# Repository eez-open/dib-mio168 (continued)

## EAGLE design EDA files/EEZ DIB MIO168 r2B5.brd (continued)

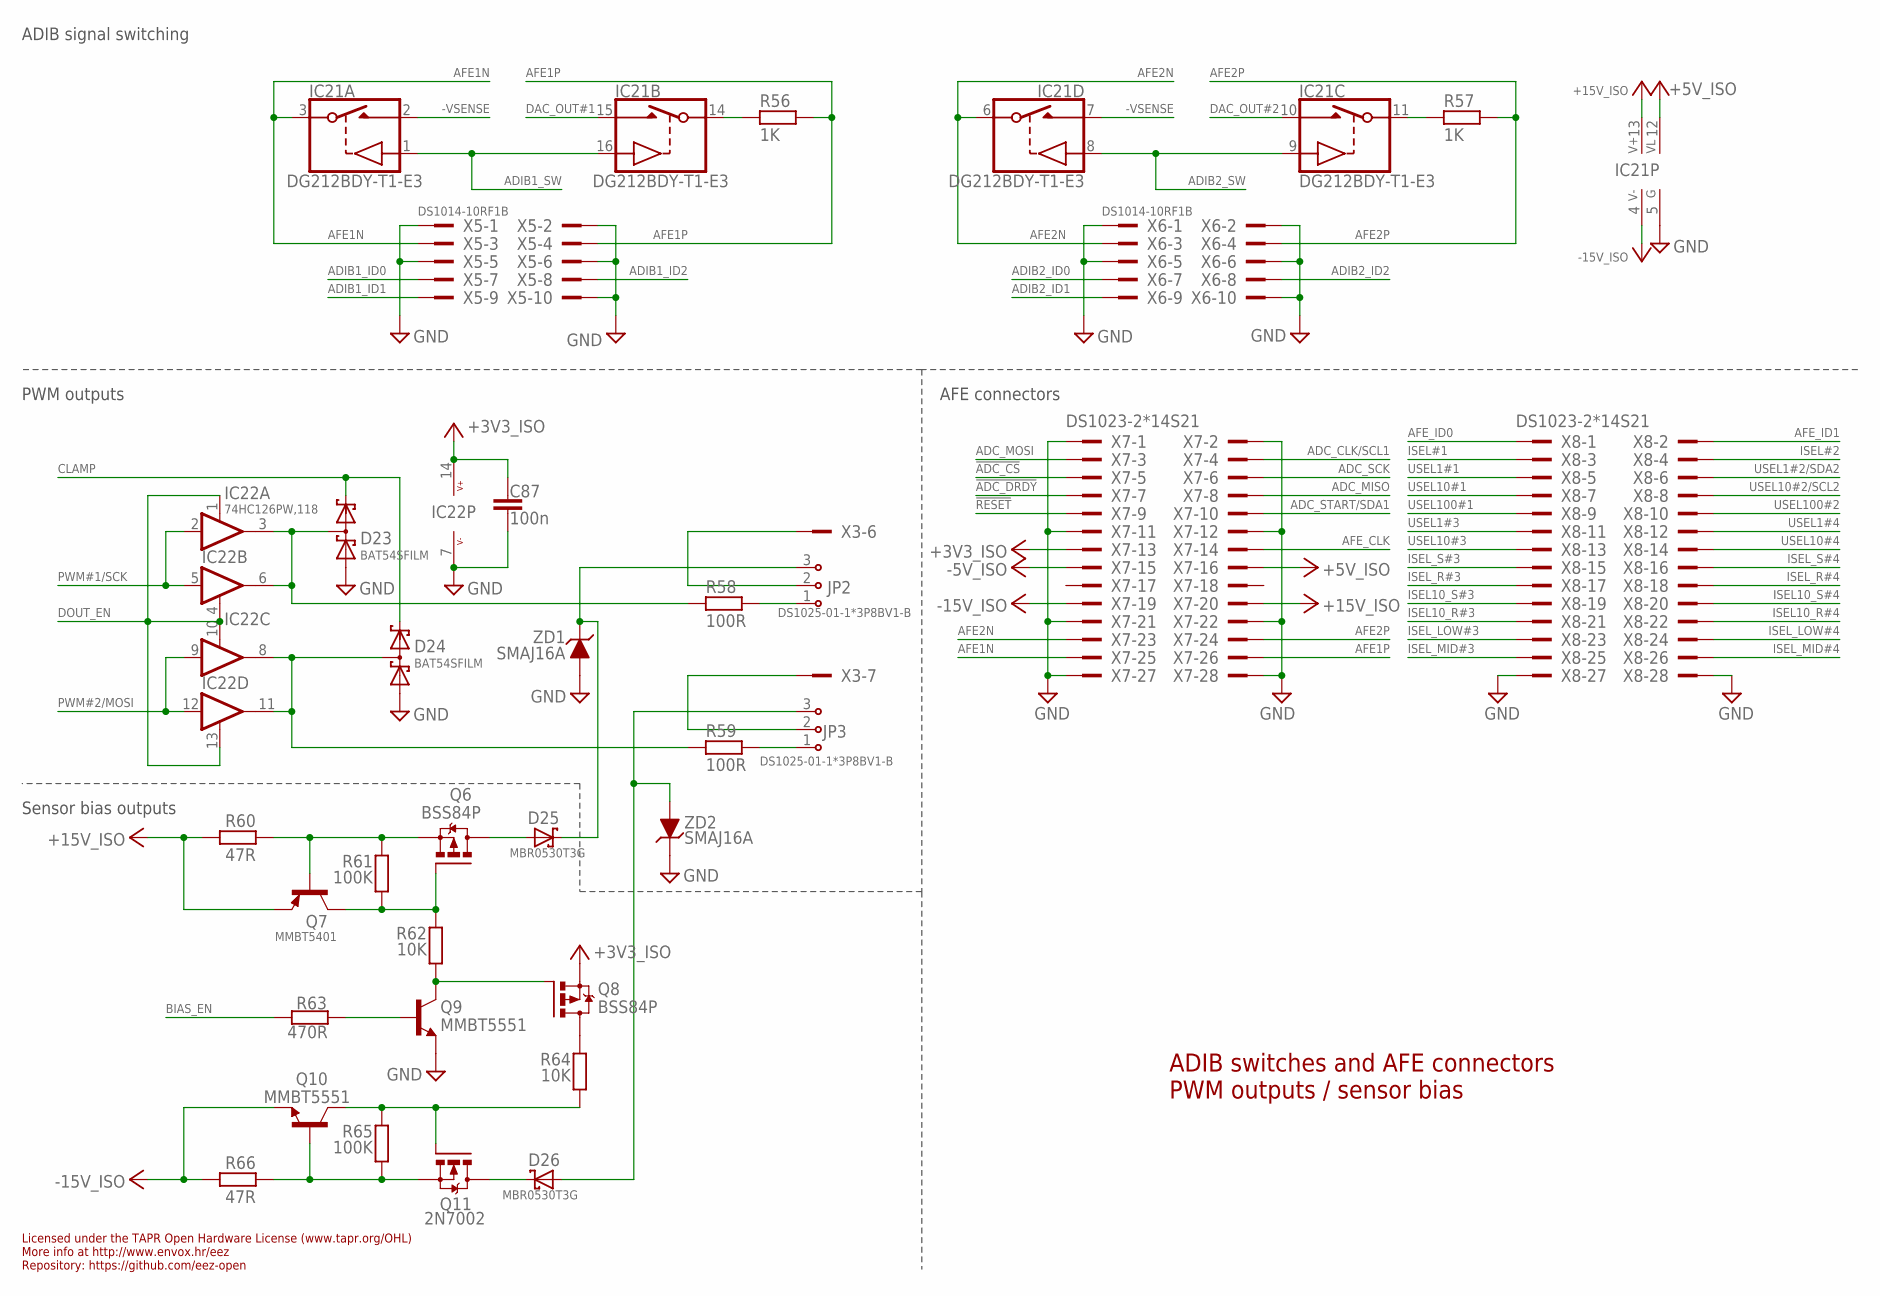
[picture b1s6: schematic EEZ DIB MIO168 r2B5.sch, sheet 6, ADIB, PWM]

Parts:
C87: 100n; C0603
D23, D24: BAT54SFILM; SOT23
D25, D26: MBR0530T3G; SOD123
IC21: DG212BDY-T1-E3; SO16
IC22: 74HC126PW,118; PW14
JP2, JP3: DS1025-01-1*3P8BV1-B; ZL303-03P
Q6, Q8: BSS84P; SOT95P237X112-3N
Q7: MMBT5401; SOT23-BEC
Q9, Q10: MMBT5551; SOT23-BEC
Q11: 2N7002; SOT103P240X110-3N
R56, R57: 1K; R0805
R58, R59: 100R; R0805
R60, R66: 47R; R0805
R61, R65: 100K; R0805
R62, R64: 10K; R0805
R63: 470R; R0805
X3: 691327310016
X5, X6: DS1014-10RF1B
X7, X8: DS1023-2*14S21; TSW-114-07-F-D
ZD1, ZD2: SMAJ16A; DO214AC

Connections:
!ADC_CS: X7.5; also elsewhere on the board
!ADC_DRDY: X7.7; also elsewhere on the board
!RESET: X7.9; also elsewhere on the board
+3V3_ISO: C87.2, IC22.14 (V+), Q8.2 (S), X7.13; also elsewhere on the board
+5V_ISO: IC21.12 (VL), X7.16; also elsewhere on the board
+15V_ISO: IC21.13 (V+), Q7.E, R60.1, X7.20; also elsewhere on the board
-5V_ISO: X7.15; also elsewhere on the board
-15V_ISO: IC21.4 (V-), Q10.E, R66.1, X7.19; also elsewhere on the board
-VSENSE: IC21.2 (D), IC21.7 (D); also elsewhere on the board
ADC_CLK/SCL1: X7.4; also elsewhere on the board
ADC_MISO: X7.8; also elsewhere on the board
ADC_MOSI: X7.3; also elsewhere on the board
ADC_SCK: X7.6; also elsewhere on the board
ADC_START/SDA1: X7.10; also elsewhere on the board
ADIB1_ID0: X5.7; also elsewhere on the board
ADIB1_ID1: X5.9; also elsewhere on the board
ADIB1_ID2: X5.8; also elsewhere on the board
ADIB1_SW: IC21.1 (IN), IC21.16 (IN); also elsewhere on the board
ADIB2_ID0: X6.7; also elsewhere on the board
ADIB2_ID1: X6.9; also elsewhere on the board
ADIB2_ID2: X6.8; also elsewhere on the board
ADIB2_SW: IC21.8 (IN), IC21.9 (IN); also elsewhere on the board
AFE1N: IC21.3 (S), X5.3, X7.25
AFE1P: R56.1, X5.4, X7.26
AFE2N: IC21.6 (S), X6.3, X7.23
AFE2P: R57.1, X6.4, X7.24
AFE_CLK: X7.14; also elsewhere on the board
AFE_ID0: X8.1; also elsewhere on the board
AFE_ID1: X8.2; also elsewhere on the board
BIAS_EN: R63.1; also elsewhere on the board
CLAMP: D23.2 (C2), D24.2 (C2); also elsewhere on the board
DAC_OUT#1: IC21.15 (D); also elsewhere on the board
DAC_OUT#2: IC21.10 (D); also elsewhere on the board
DOUT_EN: IC22.1 (EN), IC22.4 (EN), IC22.10 (EN), IC22.13 (EN); also elsewhere on the board
GND: C87.1, D23.1 (A1), D24.1 (A1), IC21.5 (GND), IC22.7 (V-), Q9.E, X5.1, X5.2, X5.5, X5.6, X5.10, X6.1, X6.2, X6.5, X6.6, X6.10, X7.1, X7.2, X7.11, X7.12, X7.21, X7.22, X7.27, X7.28, X8.27, X8.28, ZD1.A, ZD2.C; also elsewhere on the board
ISEL10_R#3: X8.21; also elsewhere on the board
ISEL10_R#4: X8.22; also elsewhere on the board
ISEL10_S#3: X8.19; also elsewhere on the board
ISEL10_S#4: X8.20; also elsewhere on the board
ISEL#1: X8.3; also elsewhere on the board
ISEL#2: X8.4; also elsewhere on the board
ISEL_LOW#3: X8.23; also elsewhere on the board
ISEL_LOW#4: X8.24; also elsewhere on the board
ISEL_MID#3: X8.25; also elsewhere on the board
ISEL_MID#4: X8.26; also elsewhere on the board
ISEL_R#3: X8.17; also elsewhere on the board
ISEL_R#4: X8.18; also elsewhere on the board
ISEL_S#3: X8.15; also elsewhere on the board
ISEL_S#4: X8.16; also elsewhere on the board
unnamed: Q9.B, R63.2
unnamed: JP2.1, R58.1
unnamed: JP3.1, R59.1
unnamed: IC21.14 (S), R56.2
unnamed: IC21.11 (S), R57.2
unnamed: JP2.2, X3.6
unnamed: JP3.2, X3.7
unnamed: D23.3 (C1A2), IC22.3 (O), IC22.6 (O), R58.2
unnamed: D24.3 (C1A2), IC22.8 (O), IC22.11 (O), R59.2
unnamed: Q8.1 (G), Q9.C, R62.2
unnamed: Q6.1 (G), Q7.C, R61.2, R62.1
unnamed: D25.A, Q6.3 (D)
unnamed: D25.C, JP2.3, ZD1.C
unnamed: Q6.2 (S), Q7.B, R60.2, R61.1
unnamed: Q10.C, Q11.1 (G), R64.2, R65.1
unnamed: Q10.B, Q11.2 (S), R65.2, R66.2
unnamed: Q8.3 (D), R64.1
unnamed: D26.C, Q11.3 (D)
unnamed: D26.A, JP3.3, ZD2.A
PWM#1/SCK: IC22.2 (I), IC22.5 (I); also elsewhere on the board
PWM#2/MOSI: IC22.9 (I), IC22.12 (I); also elsewhere on the board
USEL1#1: X8.5; also elsewhere on the board
USEL1#2/SDA2: X8.6; also elsewhere on the board
USEL1#3: X8.11; also elsewhere on the board
USEL1#4: X8.12; also elsewhere on the board
USEL10#1: X8.7; also elsewhere on the board
USEL10#2/SCL2: X8.8; also elsewhere on the board
USEL10#3: X8.13; also elsewhere on the board
USEL10#4: X8.14; also elsewhere on the board
USEL100#1: X8.9; also elsewhere on the board
USEL100#2: X8.10; also elsewhere on the board

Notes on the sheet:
Licensed under the TAPR Open Hardware License (www.tapr.org/OHL)
Repository: https://github.com/eez-open
More info at http://www.envox.hr/eez
ADIB switches and AFE connectors PWM outputs / sensor bias
ADIB signal switching
AFE connectors
PWM outputs
Sensor bias outputs

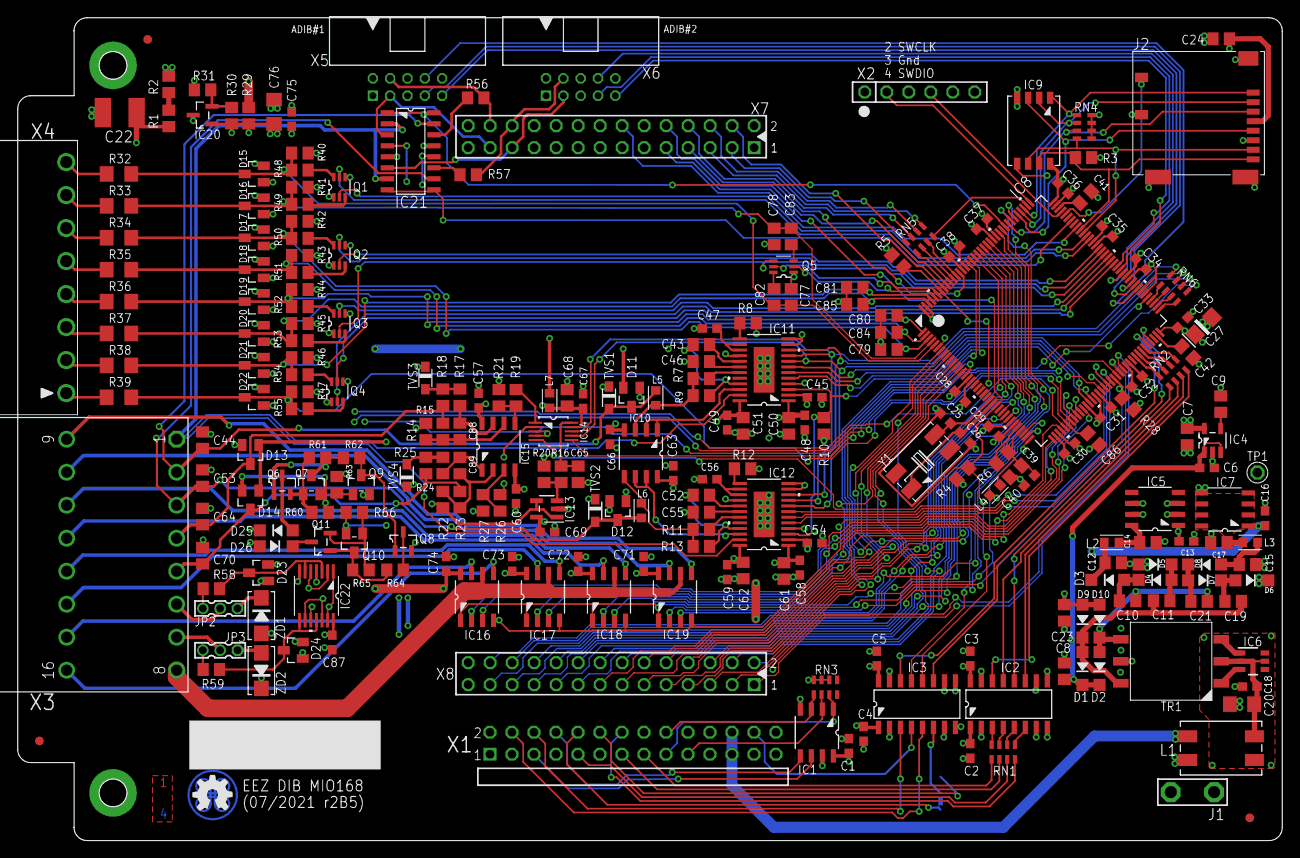
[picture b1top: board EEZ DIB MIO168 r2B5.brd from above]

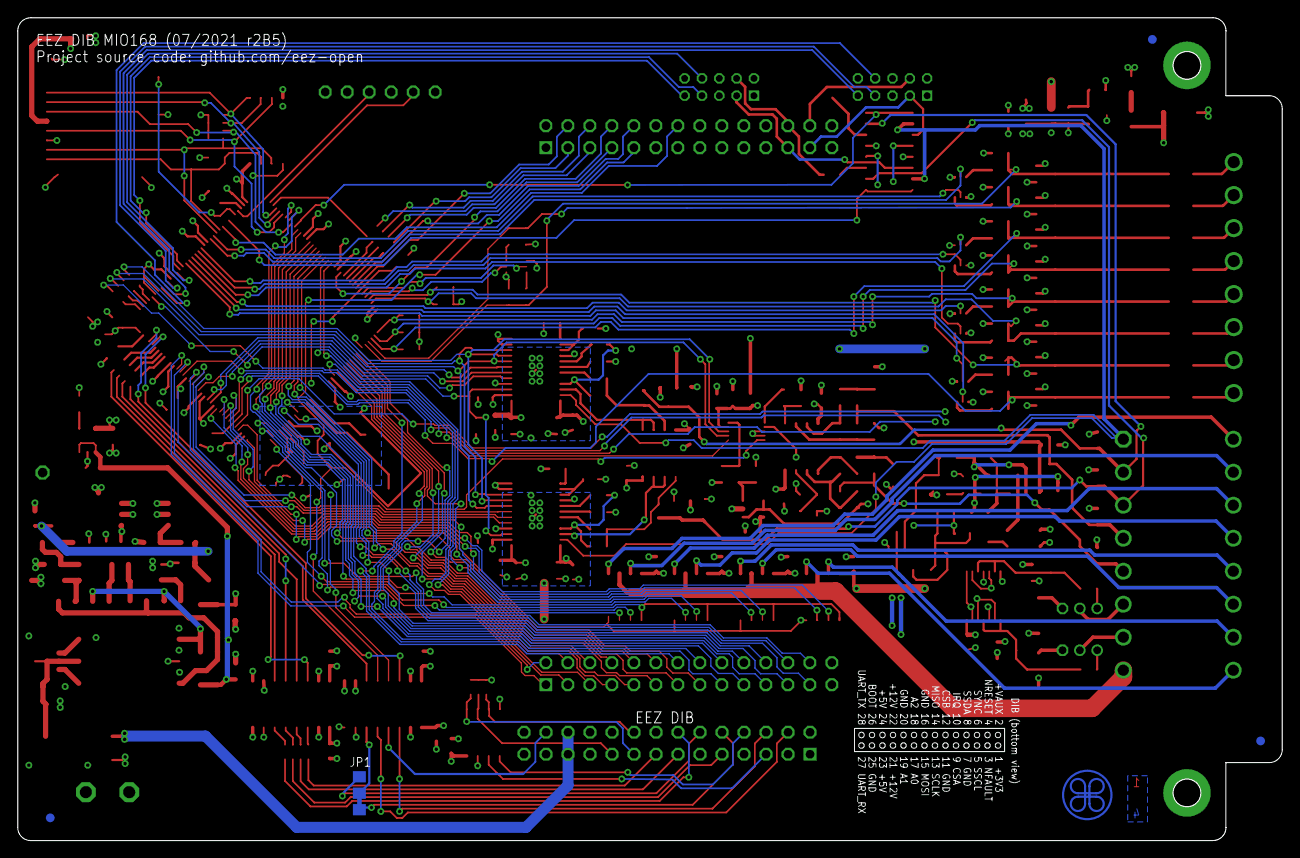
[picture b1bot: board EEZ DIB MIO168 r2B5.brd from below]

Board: 4 copper layers, 146.0 x 95.0 mm, 257 parts (2 on the bottom side), 251 nets.

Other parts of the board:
EEZ_SIGNATURE: SIGNATURESMALL; SIGNATURE_5MM

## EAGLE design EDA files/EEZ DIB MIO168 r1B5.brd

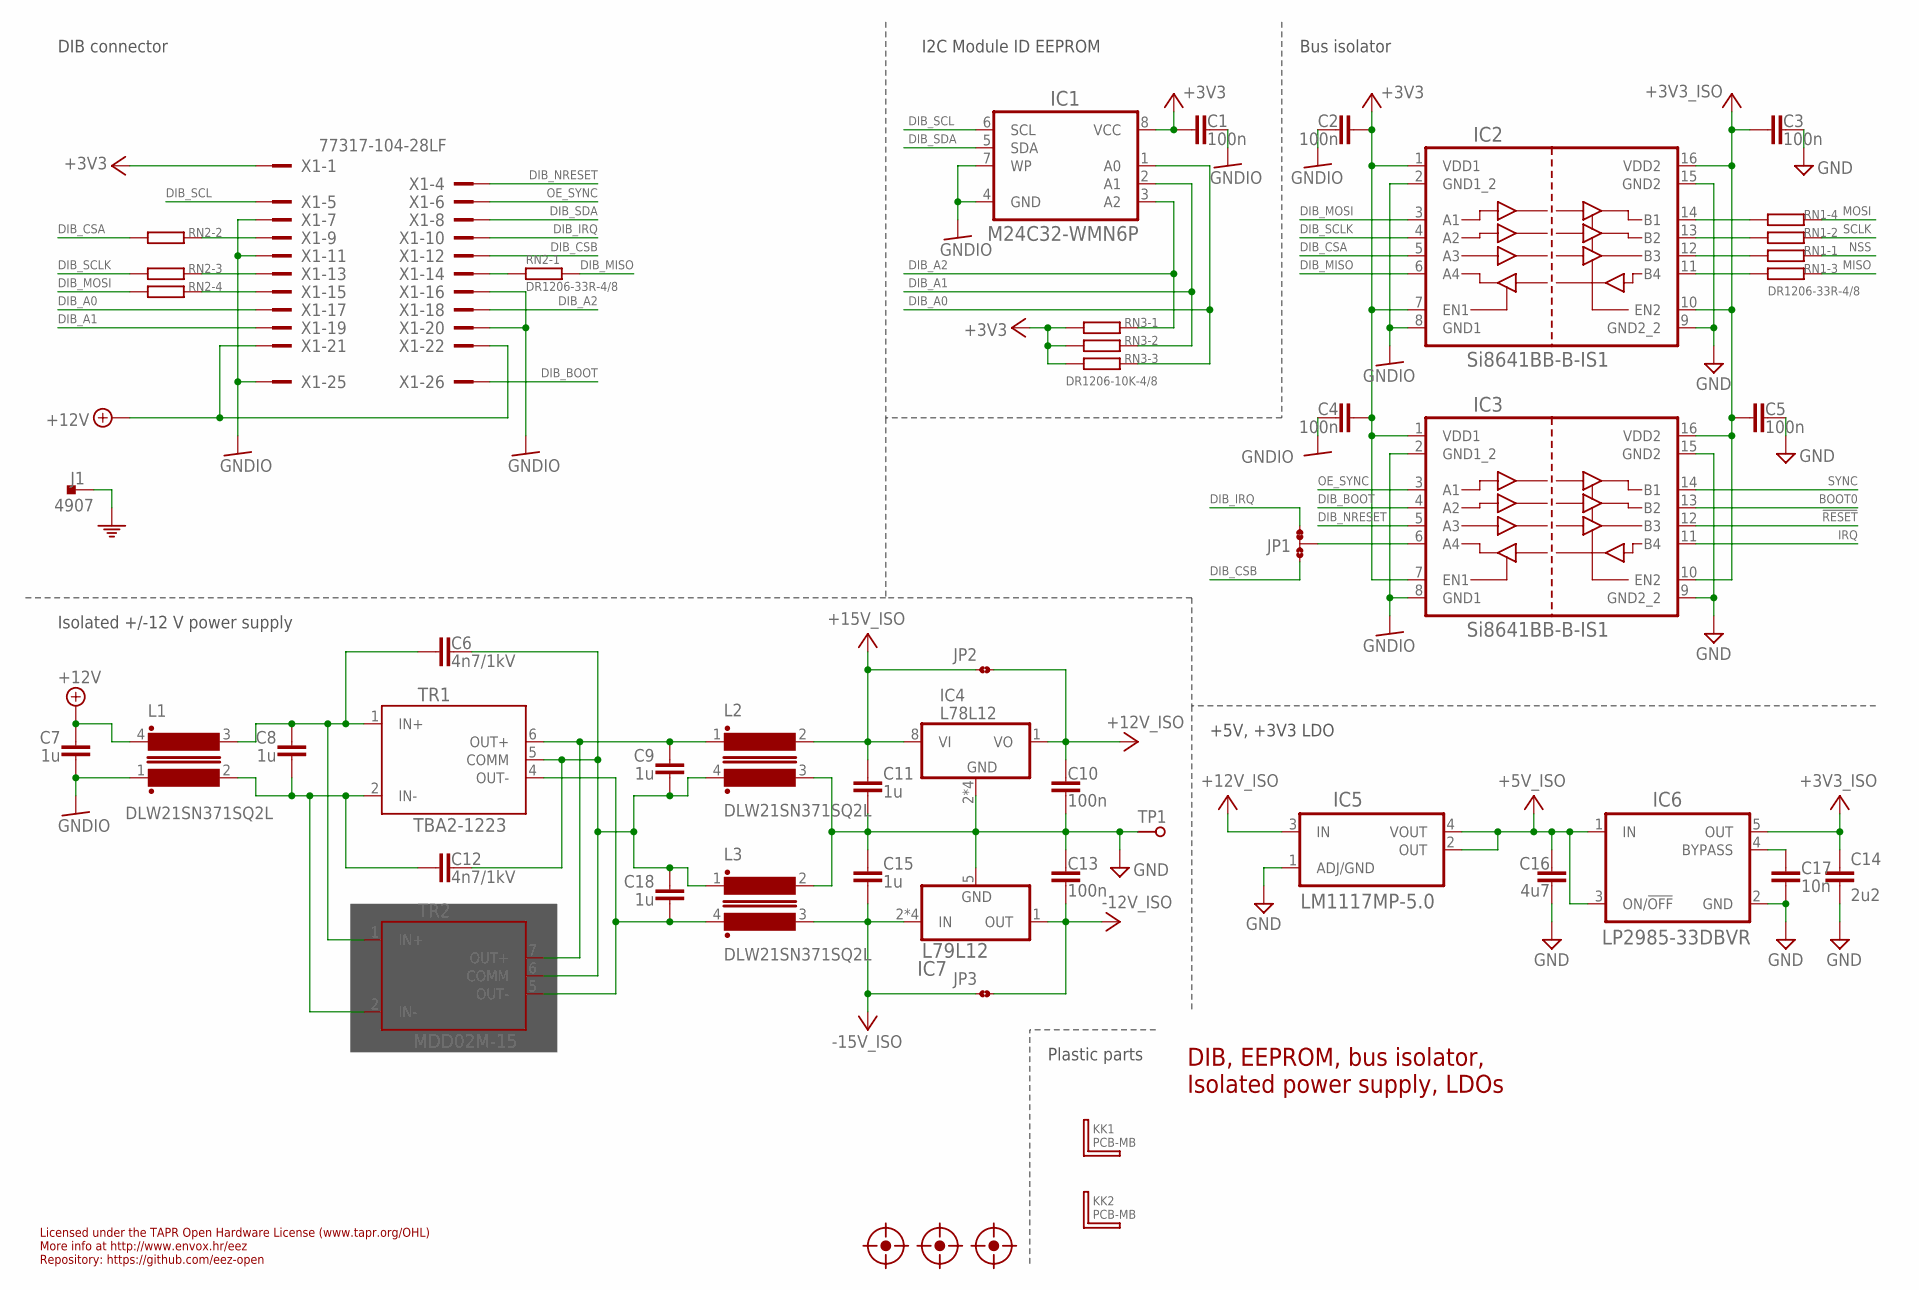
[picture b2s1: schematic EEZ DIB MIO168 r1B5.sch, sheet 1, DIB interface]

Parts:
C1, C2, C3, C4, C5, C10, C13: 100n; C0603
C6, C12: 4n7/1kV; C1812
C7, C8, C9, C11, C15, C18: 1u; C0805
C14: 2u2; C0805
C16: 4u7; C0805
C17: 10n; C0805
FM1, FM2, FM3: FIDUCIAL_2; FIDUCIAL_DUAL
IC1: M24C32-WMN6P; SOIC127P600X173-8N
IC2, IC3: Si8641BB-B-IS1; SOIC-16
IC4: L78L12; SOIC127P600X173-8N
IC5: LM1117MP-5.0; SOT230P696X180-4N
IC6: LP2985-33DBVR; SOT95P270X145-5N
IC7: L79L12; SOIC127P600X173-8N
J1: 4907; PCB_TAB-4907
JP1: JP3-CUT-0805-ROTATED; JP3-0805-CUT2
JP2, JP3: JP2-CUT-0805; R_0805
KK1, KK2: PCB-MB
L1, L2, L3: DLW21SN371SQ2L; MURATA_DLW21S
RN1, RN2: DR1206-33R-4/8; CAY16
RN3: DR1206-10K-4/8; CAY16
TP1: PCB_TEST_TABSHIELD; PCB_SHIELD_TAB
TR1: TBA2-1223; TBA2
TR2: MDD02M-15; MDD02
X1: 77317-104-28LF

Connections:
!RESET: IC3.12 (B3); also elsewhere on the board
+3V3: C1.2, C2.1, C4.1, IC1.8 (VCC), IC2.1 (VDD1), IC2.7 (EN1), IC3.1 (VDD1), IC3.7 (EN1), RN3.6 (2), RN3.7 (2), RN3.8 (2), X1.1
+3V3_ISO: C3.2, C5.2, C14.1, IC2.10 (EN2), IC2.16 (VDD2), IC3.10 (EN2), IC3.16 (VDD2), IC6.5 (OUT); also elsewhere on the board
+5V_ISO: C16.2, IC5.2 (OUT), IC5.4 (VOUT), IC6.1 (IN), IC6.3 (ON/!OFF); also elsewhere on the board
+12V: C7.2, L1.4, X1.21, X1.22
+12V_CM: C6.1, C8.2, L1.3, TR1.1 (IN+), TR2.1 (IN+)
+12V_ISO: C10.1, IC4.1 (VO), IC5.3 (IN), JP2.2; also elsewhere on the board
+15V_ISO: C11.2, IC4.8 (VI), JP2.1, L2.2; also elsewhere on the board
-12V_ISO: C13.2, IC7.1 (OUT), JP3.2; also elsewhere on the board
-15V_ISO: C15.1, IC7.2 (IN), IC7.3 (IN), IC7.6 (IN), IC7.7 (IN), JP3.1, L3.3; also elsewhere on the board
BOOT0: IC3.13 (B2); also elsewhere on the board
DIB_A0: IC1.1 (A0), RN3.3 (1), X1.17
DIB_A1: IC1.2 (A1), RN3.2 (1), X1.19
DIB_A2: IC1.3 (A2), RN3.1, X1.18
DIB_BOOT: IC3.4 (A2), X1.26
DIB_CSA: IC2.5 (A3), RN2.2 (1)
DIB_CSB: JP1.NO, X1.12
DIB_IRQ: JP1.NC, X1.10
DIB_MISO: IC2.6 (A4), RN2.1
DIB_MOSI: IC2.3 (A1), RN2.4 (1)
DIB_NRESET: IC3.5 (A3), X1.4
DIB_SCL: IC1.6 (SCL), X1.5
DIB_SCLK: IC2.4 (A2), RN2.3 (1)
DIB_SDA: IC1.5 (SDA), X1.8
GND: C3.1, C5.1, C10.2, C11.1, C13.1, C14.2, C15.2, C16.1, C17.1, IC2.9 (GND2_2), IC2.15 (GND2), IC3.9 (GND2_2), IC3.15 (GND2), IC4.2 (GND), IC4.3 (GND), IC4.6 (GND), IC4.7 (GND), IC5.1 (ADJ/GND), IC6.2 (GND), IC7.5 (GND), L2.3, L3.2, TP1.1; also elsewhere on the board
GNDIO: C1.1, C2.2, C4.2, C7.1, IC1.4 (GND), IC1.7 (WP), IC2.2 (GND1_2), IC2.8 (GND1), IC3.2 (GND1_2), IC3.8 (GND1), L1.1, X1.7, X1.11, X1.16, X1.20, X1.25
GND_CM: C8.1, C12.1, L1.2, TR1.2 (IN-), TR2.2 (IN-)
IRQ: IC3.11 (B4); also elsewhere on the board
MISO: RN1.6 (2); also elsewhere on the board
MOSI: RN1.5 (2); also elsewhere on the board
unnamed: IC3.6 (A4), JP1.COM
unnamed: IC2.14 (B1), RN1.4 (1)
unnamed: C9.2, L2.1, TR1.6 (OUT+), TR2.7 (OUT+)
unnamed: C6.2, C9.1, C12.2, C18.2, L2.4, L3.1, TR1.5 (COMM), TR2.6 (COMM)
unnamed: C18.1, L3.4, TR1.4 (OUT-), TR2.5 (OUT-)
unnamed: RN2.7 (2), X1.9
unnamed: IC2.11 (B4), RN1.3 (1)
unnamed: RN2.6 (2), X1.13
unnamed: RN2.8 (2), X1.14
unnamed: RN2.5 (2), X1.15
unnamed: C17.2, IC6.4 (BYPASS)
unnamed: IC2.13 (B2), RN1.2 (1)
unnamed: IC2.12 (B3), RN1.1
NSS: RN1.8 (2); also elsewhere on the board
OE_SYNC: IC3.3 (A1), X1.6
PE: J1.1, J1.2; also elsewhere on the board
SCLK: RN1.7 (2); also elsewhere on the board
SYNC: IC3.14 (B1); also elsewhere on the board

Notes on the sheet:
Licensed under the TAPR Open Hardware License (www.tapr.org/OHL)
Repository: https://github.com/eez-open
More info at http://www.envox.hr/eez
DIB, EEPROM, bus isolator, Isolated power supply, LDOs
Plastic parts
I2C Module ID EEPROM
+5V, +3V3 LDO
Bus isolator
Isolated +/-12 V power supply
DIB connector

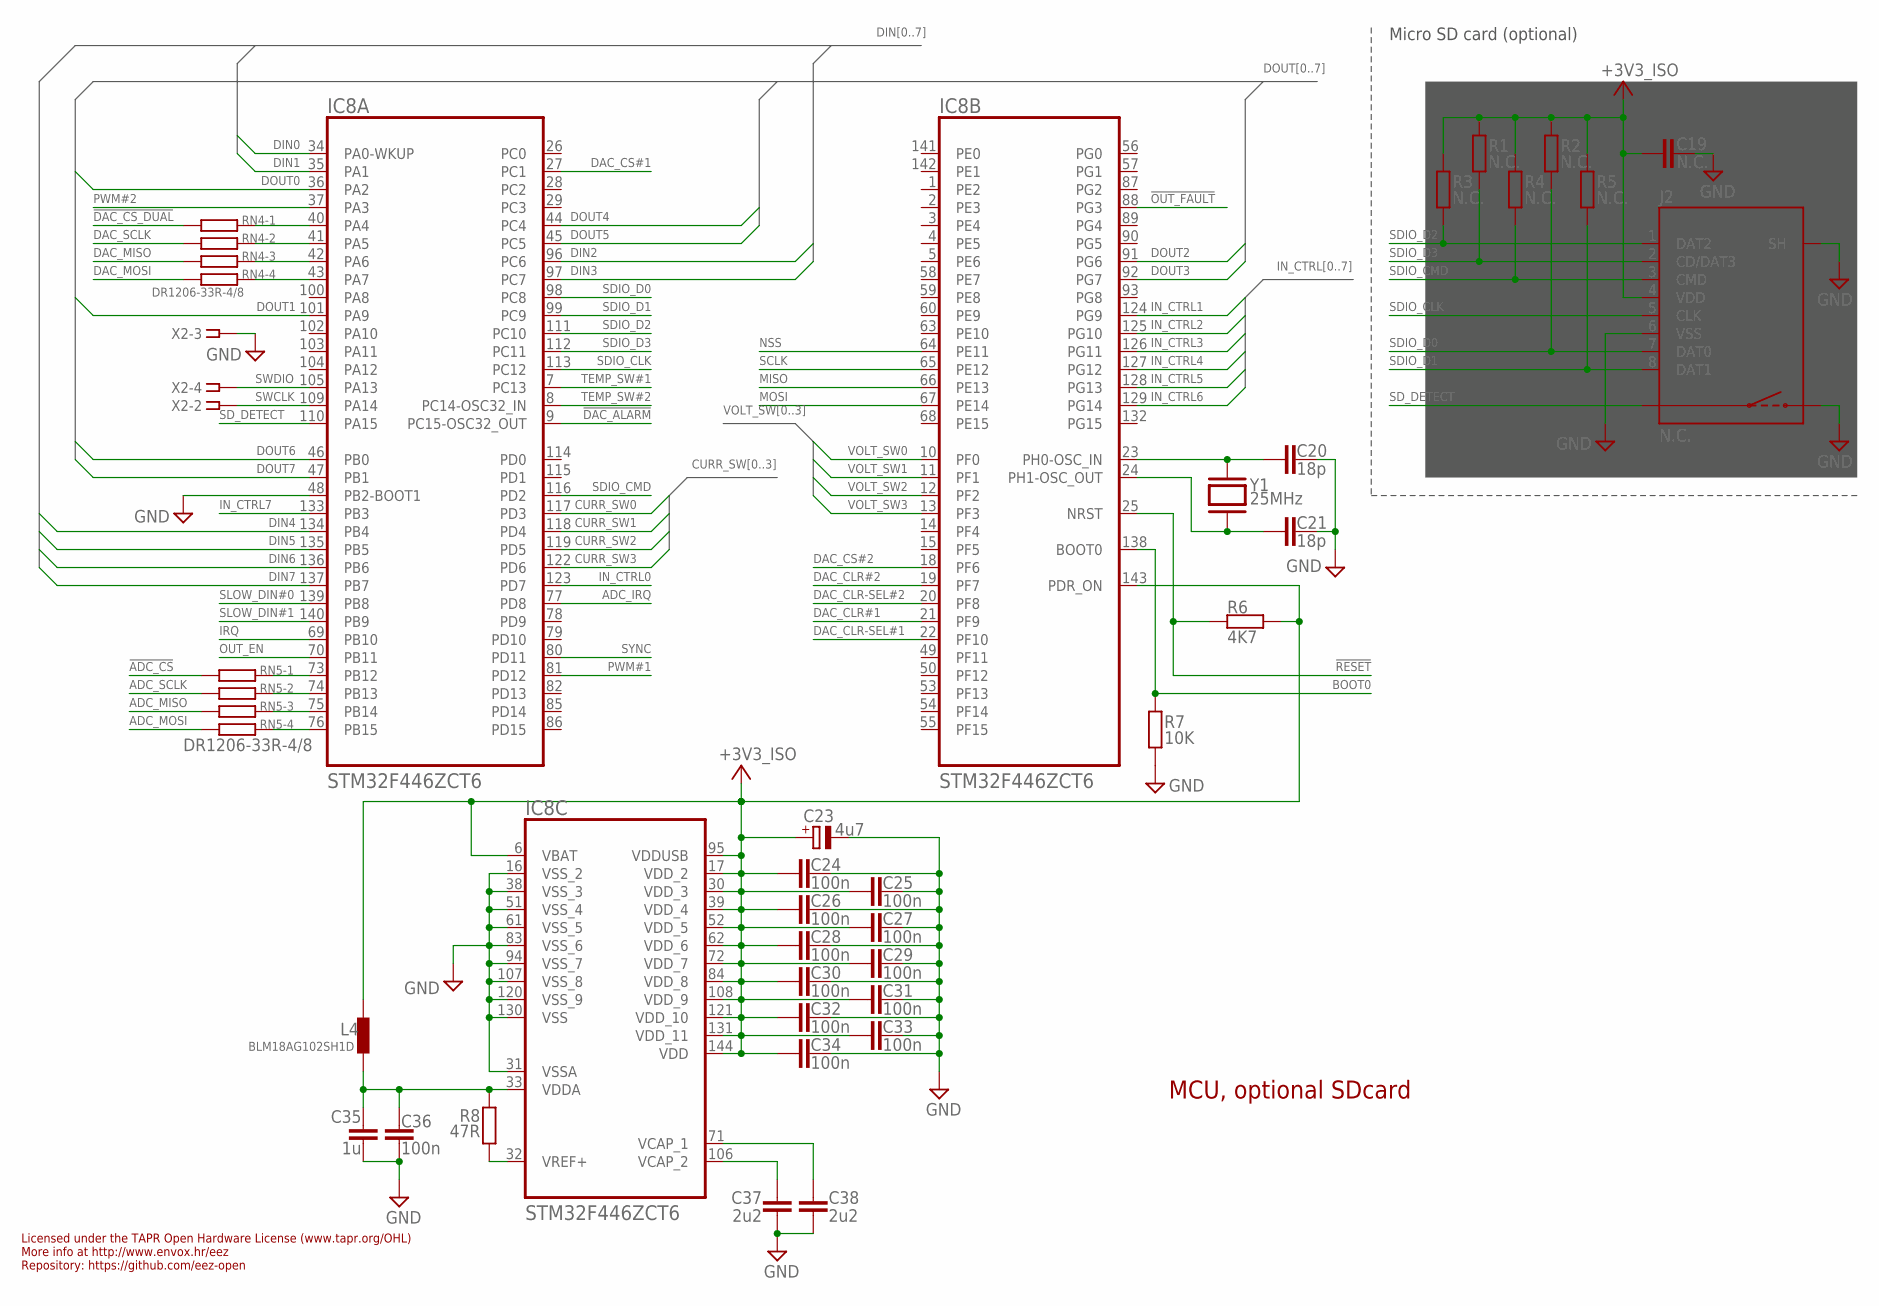
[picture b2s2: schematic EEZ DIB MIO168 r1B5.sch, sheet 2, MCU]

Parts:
C19: N.C.; C0805
C20, C21: 18p; C0603
C23: 4u7; EC1206
C24, C25, C26, C27, C28, C29, C30, C31, C32, C33, C34, C36: 100n; C0603
C35: 1u; C0805
C37, C38: 2u2; C0805
IC8: STM32F446ZCT6; LQFP-144
J2: N.C.; 5033981892
L4: BLM18AG102SH1D; BEAD0603
R1, R2, R3, R4, R5: N.C.; R0805
R6: 4K7; R0805
R7: 10K; R0805
R8: 47R; R0805
RN4, RN5: DR1206-33R-4/8; CAY16
X2: SSW-106-02-S-S
Y1: 25MHz; HC-49/4H

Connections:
!ADC_CS: RN5.1; also elsewhere on the board
!DAC_ALARM: IC8.9 (PC15-OSC32_OUT); also elsewhere on the board
!DAC_CS_DUAL: RN4.1; also elsewhere on the board
!OUT_FAULT: IC8.88 (PG3); also elsewhere on the board
!RESET: IC8.25 (NRST), R6.2; also elsewhere on the board
+3V3_ISO: C19.1, C23.+, C24.1, C25.1, C26.1, C27.1, C28.1, C29.1, C30.1, C31.1, C32.1, C33.1, C34.1, IC8.6 (VBAT), IC8.17 (VDD_2), IC8.30 (VDD_3), IC8.39 (VDD_4), IC8.52 (VDD_5), IC8.62 (VDD_6), IC8.72 (VDD_7), IC8.84 (VDD_8), IC8.95 (VDDUSB), IC8.108 (VDD_9), IC8.121 (VDD_10), IC8.131 (VDD_11), IC8.143 (PDR_ON), IC8.144 (VDD), J2.4 (VDD), L4.P$1 (1), R1.1, R2.1, R3.1, R4.1, R5.1, R6.1; also elsewhere on the board
ADC_IRQ: IC8.77 (PD8); also elsewhere on the board
ADC_MISO: RN5.3 (1); also elsewhere on the board
ADC_MOSI: RN5.4 (1); also elsewhere on the board
ADC_SCLK: RN5.2 (1); also elsewhere on the board
BOOT0: IC8.138 (BOOT0), R7.2; also elsewhere on the board
CURR_SW0: IC8.117 (PD3); also elsewhere on the board
CURR_SW1: IC8.118 (PD4); also elsewhere on the board
CURR_SW2: IC8.119 (PD5); also elsewhere on the board
CURR_SW3: IC8.122 (PD6); also elsewhere on the board
DAC_CLR#1: IC8.21 (PF9); also elsewhere on the board
DAC_CLR#2: IC8.19 (PF7); also elsewhere on the board
DAC_CLR-SEL#1: IC8.22 (PF10); also elsewhere on the board
DAC_CLR-SEL#2: IC8.20 (PF8); also elsewhere on the board
DAC_CS#1: IC8.27 (PC1); also elsewhere on the board
DAC_CS#2: IC8.18 (PF6); also elsewhere on the board
DAC_MISO: RN4.3 (1); also elsewhere on the board
DAC_MOSI: RN4.4 (1); also elsewhere on the board
DAC_SCLK: RN4.2 (1); also elsewhere on the board
DIN0: IC8.34 (PA0-WKUP); also elsewhere on the board
DIN1: IC8.35 (PA1); also elsewhere on the board
DIN2: IC8.96 (PC6); also elsewhere on the board
DIN3: IC8.97 (PC7); also elsewhere on the board
DIN4: IC8.134 (PB4); also elsewhere on the board
DIN5: IC8.135 (PB5); also elsewhere on the board
DIN6: IC8.136 (PB6); also elsewhere on the board
DIN7: IC8.137 (PB7); also elsewhere on the board
DOUT0: IC8.36 (PA2); also elsewhere on the board
DOUT1: IC8.101 (PA9); also elsewhere on the board
DOUT2: IC8.91 (PG6); also elsewhere on the board
DOUT3: IC8.92 (PG7); also elsewhere on the board
DOUT4: IC8.44 (PC4); also elsewhere on the board
DOUT5: IC8.45 (PC5); also elsewhere on the board
DOUT6: IC8.46 (PB0); also elsewhere on the board
DOUT7: IC8.47 (PB1); also elsewhere on the board
GND: C19.2, C20.1, C21.1, C23.-, C24.2, C25.2, C26.2, C27.2, C28.2, C29.2, C30.2, C31.2, C32.2, C33.2, C34.2, C35.2, C36.2, C37.1, C38.1, IC8.16 (VSS_2), IC8.31 (VSSA), IC8.38 (VSS_3), IC8.48 (PB2-BOOT1), IC8.51 (VSS_4), IC8.61 (VSS_5), IC8.83 (VSS_6), IC8.94 (VSS_7), IC8.107 (VSS_8), IC8.120 (VSS_9), IC8.130 (VSS), J2.6 (VSS), J2.S (SH), J2.S1 (SH), J2.S2 (SH), J2.SW2, R7.1, X2.3; also elsewhere on the board
IN_CTRL0: IC8.123 (PD7); also elsewhere on the board
IN_CTRL1: IC8.124 (PG9); also elsewhere on the board
IN_CTRL2: IC8.125 (PG10); also elsewhere on the board
IN_CTRL3: IC8.126 (PG11); also elsewhere on the board
IN_CTRL4: IC8.127 (PG12); also elsewhere on the board
IN_CTRL5: IC8.128 (PG13); also elsewhere on the board
IN_CTRL6: IC8.129 (PG14); also elsewhere on the board
IN_CTRL7: IC8.133 (PB3); also elsewhere on the board
IRQ: IC8.69 (PB10); also elsewhere on the board
MISO: IC8.66 (PE13); also elsewhere on the board
MOSI: IC8.67 (PE14); also elsewhere on the board
unnamed: IC8.75 (PB14), RN5.6 (2)
unnamed: IC8.76 (PB15), RN5.5 (2)
unnamed: IC8.73 (PB12), RN5.8 (2)
unnamed: IC8.74 (PB13), RN5.7 (2)
unnamed: IC8.40 (PA4), RN4.8 (2)
unnamed: C37.2, IC8.106 (VCAP_2)
unnamed: IC8.41 (PA5), RN4.7 (2)
unnamed: IC8.42 (PA6), RN4.6 (2)
unnamed: IC8.43 (PA7), RN4.5 (2)
unnamed: C38.2, IC8.71 (VCAP_1)
unnamed: C35.1, C36.1, IC8.33 (VDDA), L4.P$2 (2), R8.1
unnamed: IC8.32 (VREF+), R8.2
NSS: IC8.64 (PE11); also elsewhere on the board
OUT_EN: IC8.70 (PB11); also elsewhere on the board
PWM#1: IC8.81 (PD12); also elsewhere on the board
PWM#2: IC8.37 (PA3); also elsewhere on the board
RCC_OSC_IN: C20.2, IC8.23 (PH0-OSC_IN), Y1.2
RCC_OSC_OUT: C21.2, IC8.24 (PH1-OSC_OUT), Y1.1
SCLK: IC8.65 (PE12); also elsewhere on the board
SDIO_CLK: IC8.113 (PC12), J2.5 (CLK)
SDIO_CMD: IC8.116 (PD2), J2.3 (CMD), R4.2
SDIO_D0: IC8.98 (PC8), J2.7 (DAT0), R2.2
SDIO_D1: IC8.99 (PC9), J2.8 (DAT1), R5.2
SDIO_D2: IC8.111 (PC10), J2.1 (DAT2), R3.2
SDIO_D3: IC8.112 (PC11), J2.2 (CD/DAT3), R1.2
SD_DETECT: IC8.110 (PA15), J2.SW1
SLOW_DIN#0: IC8.139 (PB8); also elsewhere on the board
SLOW_DIN#1: IC8.140 (PB9); also elsewhere on the board
SWCLK: IC8.109 (PA14), X2.2
SWDIO: IC8.105 (PA13), X2.4
SYNC: IC8.80 (PD11); also elsewhere on the board
TEMP_SW#1: IC8.7 (PC13); also elsewhere on the board
TEMP_SW#2: IC8.8 (PC14-OSC32_IN); also elsewhere on the board
VOLT_SW0: IC8.10 (PF0); also elsewhere on the board
VOLT_SW1: IC8.11 (PF1); also elsewhere on the board
VOLT_SW2: IC8.12 (PF2); also elsewhere on the board
VOLT_SW3: IC8.13 (PF3); also elsewhere on the board

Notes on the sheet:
Licensed under the TAPR Open Hardware License (www.tapr.org/OHL)
Repository: https://github.com/eez-open
More info at http://www.envox.hr/eez
MCU, optional SDcard
Micro SD card (optional)

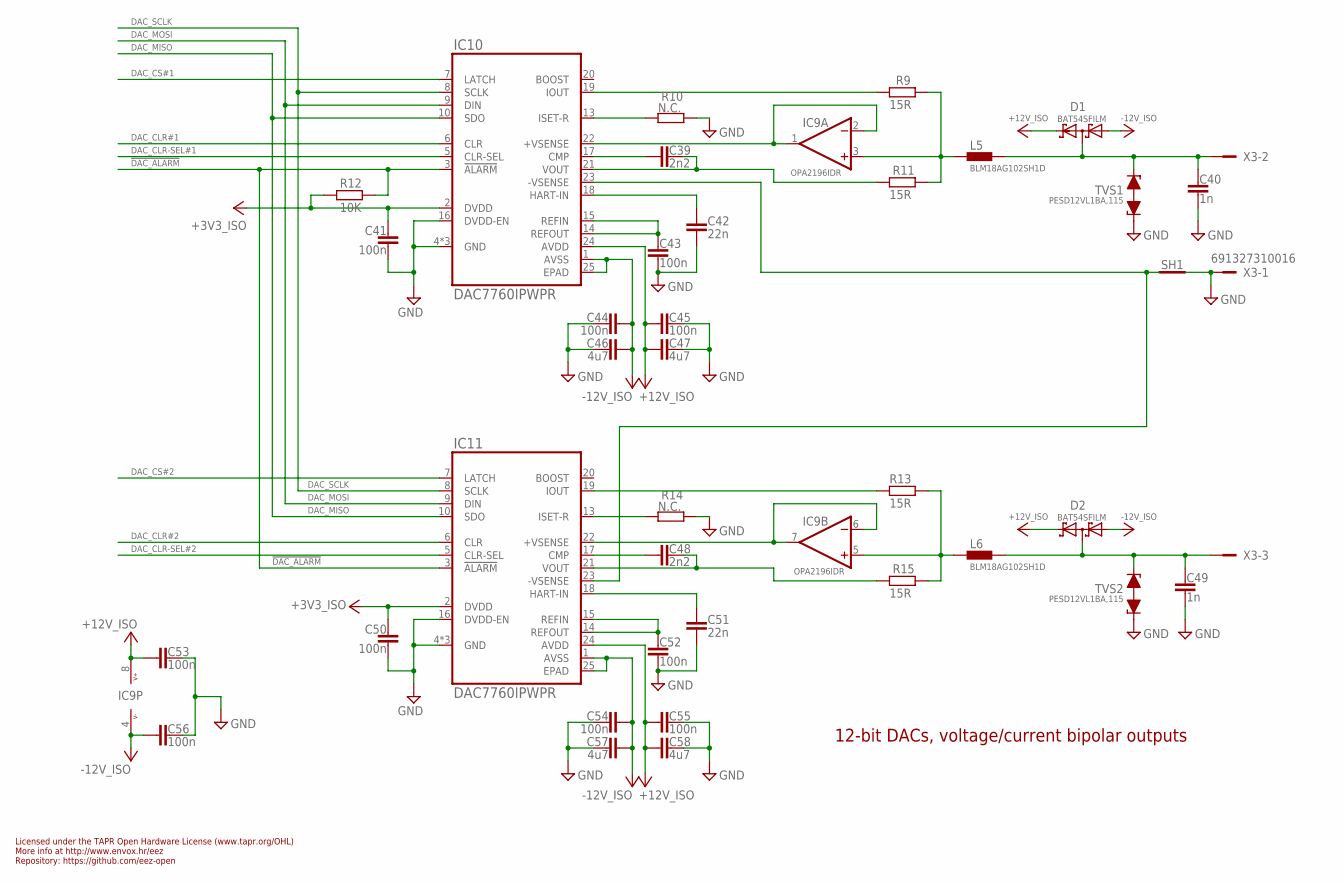
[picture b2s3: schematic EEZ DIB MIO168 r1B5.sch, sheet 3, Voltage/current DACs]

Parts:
C39, C48: 2n2; C0805
C40, C49: 1n; C0805
C41, C43, C44, C45, C50, C52, C53, C54, C55, C56: 100n; C0603
C42, C51: 22n; C0805
C46, C47, C57, C58: 4u7; C0805
D1, D2: BAT54SFILM; SOT23
IC9: OPA2196IDR; SOIC127P600X173-8N
IC10, IC11: DAC7760IPWPR; PWP24
L5, L6: BLM18AG102SH1D; BEAD0603
R9, R11, R13, R15: 15R; R0805
R10, R14: N.C.; R0805
R12: 10K; R0805
SH1: SHORTNOHOLE; SHORT_NOHOLE
TVS1, TVS2: PESD12VL1BA,115; SOD323-BIDIR
X3: 691327310016

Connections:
!DAC_ALARM: IC10.3 (!ALARM), IC11.3 (!ALARM), R12.2; also elsewhere on the board
+3V3_ISO: C41.1, C50.1, IC10.2 (DVDD), IC11.2 (DVDD), R12.1; also elsewhere on the board
+12V_ISO: C45.1, C47.2, C53.1, C55.1, C58.2, D1.2 (C2), D2.2 (C2), IC9.8 (V+), IC10.24 (AVDD), IC11.24 (AVDD); also elsewhere on the board
+VSENSE1: IC9.1 (OUT), IC9.2 (-IN), IC10.22 (+VSENSE)
+VSENSE2: IC9.6 (-IN), IC9.7 (OUT), IC11.22 (+VSENSE)
-12V_ISO: C44.1, C46.2, C54.1, C56.1, C57.2, D1.1 (A1), D2.1 (A1), IC9.4 (V-), IC10.1 (AVSS), IC10.25 (EPAD), IC11.1 (AVSS), IC11.25 (EPAD); also elsewhere on the board
-VSENSE: IC10.23 (-VSENSE), IC11.23 (-VSENSE), SH1.2 (GND_B)
DAC_CLR#1: IC10.6 (CLR); also elsewhere on the board
DAC_CLR#2: IC11.6 (CLR); also elsewhere on the board
DAC_CLR-SEL#1: IC10.5 (CLR-SEL); also elsewhere on the board
DAC_CLR-SEL#2: IC11.5 (CLR-SEL); also elsewhere on the board
DAC_CS#1: IC10.7 (LATCH); also elsewhere on the board
DAC_CS#2: IC11.7 (LATCH); also elsewhere on the board
DAC_MISO: IC10.10 (SDO), IC11.10 (SDO); also elsewhere on the board
DAC_MOSI: IC10.9 (DIN), IC11.9 (DIN); also elsewhere on the board
DAC_OUT#1: C40.1, D1.3 (C1A2), L5.P$2 (2), TVS1.C2 (2), X3.2
DAC_OUT#2: C49.1, D2.3 (C1A2), L6.P$2 (2), TVS2.C2 (2), X3.3
DAC_SCLK: IC10.8 (SCLK), IC11.8 (SCLK); also elsewhere on the board
GND: C40.2, C41.2, C42.1, C43.2, C44.2, C45.2, C46.1, C47.1, C49.2, C50.2, C51.1, C52.2, C53.2, C54.2, C55.2, C56.2, C57.1, C58.1, IC10.4 (GND), IC10.11 (GND), IC10.12 (GND), IC10.16 (DVDD-EN), IC11.4 (GND), IC11.11 (GND), IC11.12 (GND), IC11.16 (DVDD-EN), R10.1, R14.1, SH1.1 (GND_A), TVS1.C1 (1), TVS2.C1 (1), X3.1; also elsewhere on the board
HART#1: C42.2, IC10.18 (HART-IN)
HART#2: C51.2, IC11.18 (HART-IN)
unnamed: C48.2, IC11.17 (CMP)
unnamed: C48.1, IC11.21 (VOUT), R15.2
unnamed: IC9.5 (+IN), L6.P$1 (1), R13.1, R15.1
unnamed: IC11.19 (IOUT), R13.2
unnamed: C52.1, IC11.14 (REFOUT), IC11.15 (REFIN)
unnamed: C39.2, IC10.17 (CMP)
unnamed: IC9.3 (+IN), L5.P$1 (1), R9.1, R11.1
unnamed: C43.1, IC10.14 (REFOUT), IC10.15 (REFIN)
unnamed: IC11.13 (ISET-R), R14.2
unnamed: IC10.13 (ISET-R), R10.2
unnamed: C39.1, IC10.21 (VOUT), R11.2
unnamed: IC10.19 (IOUT), R9.2

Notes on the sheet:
Licensed under the TAPR Open Hardware License (www.tapr.org/OHL)
Repository: https://github.com/eez-open
More info at http://www.envox.hr/eez
12-bit DACs, voltage/current bipolar outputs
